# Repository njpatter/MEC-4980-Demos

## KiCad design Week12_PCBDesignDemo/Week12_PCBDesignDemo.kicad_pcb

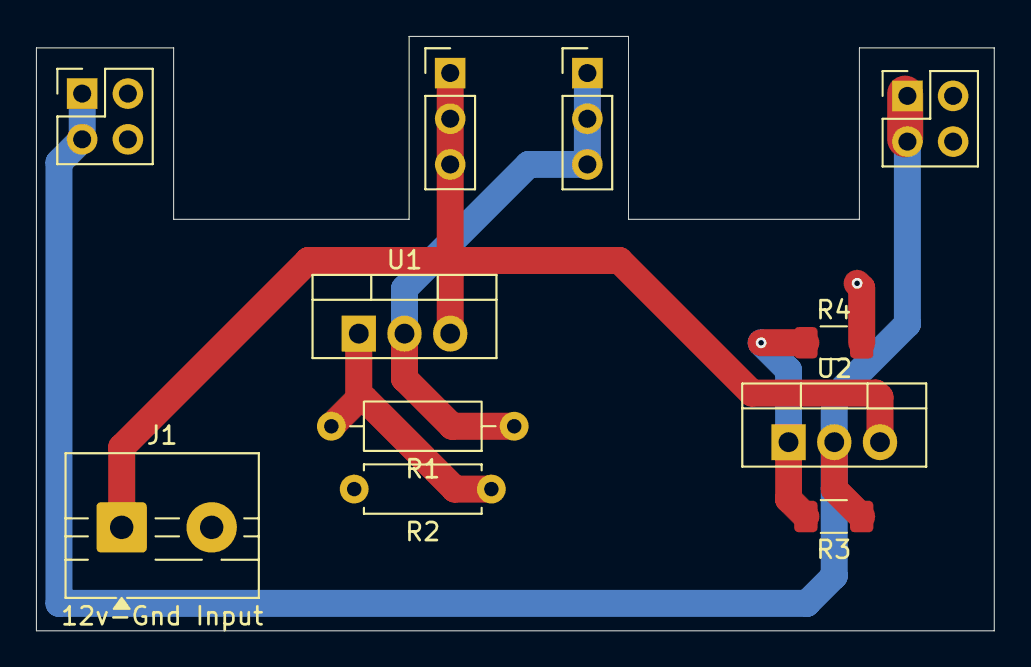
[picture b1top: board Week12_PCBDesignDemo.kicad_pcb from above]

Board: 2 copper layers, 53.2 x 33.0 mm, 11 parts (0 on the bottom side), 6 nets.

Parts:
J1: 12v-Gnd Input; TerminalBlock_MaiXu_MX126-5.0-02P_1x02_P5.00mm
J2, J3: 3.3-Gnd; PinHeader_2x02_P2.54mm_Vertical
J4: 12v; PinHeader_1x03_P2.54mm_Vertical
J5: 5v; PinHeader_1x03_P2.54mm_Vertical
R1: 120; R_Axial_DIN0207_L6.3mm_D2.5mm_P10.16mm_Horizontal
R2: 360; R_Axial_DIN0207_L6.3mm_D2.5mm_P7.62mm_Horizontal
R3: 120; R_1206_3216Metric_Pad1.30x1.75mm_HandSolder
R4: 200; R_1206_3216Metric_Pad1.30x1.75mm_HandSolder
U1: 5V Regulator; TO-220-3_Vertical
U2: 3.3v Regulator; TO-220-3_Vertical

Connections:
+3.3V: J2.1, J2.3, J3.1, J3.3, R3.1, U2.2 (VO)
+5V: J5.1, J5.2, J5.3, R1.1, U1.2 (VO)
+12V: J1.1, J4.1, J4.2, J4.3, U1.3 (VI), U2.3 (VI)
GND: J1.2, J2.2, J2.4, J3.2, J3.4, R2.2, R4.2
unnamed: R1.2, R2.1, U1.1 (ADJ)
unnamed: R3.2, R4.1, U2.1 (ADJ)

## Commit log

2025-09-17 Week 2 Friday and Week 3 Monday code
2025-09-17 Week3Monday now lab 03!
2025-09-23 Added Pin Interrupt example for start of week 4
2025-09-26 Updated to where I stopped on Wednesday of Week 4
2025-09-26 Updated through Friday's class
2025-10-02 Week 5 - Sorting Line Demo added!
2025-10-07 Added initial Week 6 code
2025-10-08 Working Motor Encoder code for midterm project
2025-10-29 Added Stepper Motor Code for Week 9
2025-11-07 Added Simple CNC Example
2025-11-21 Added power supply example from Week 12
